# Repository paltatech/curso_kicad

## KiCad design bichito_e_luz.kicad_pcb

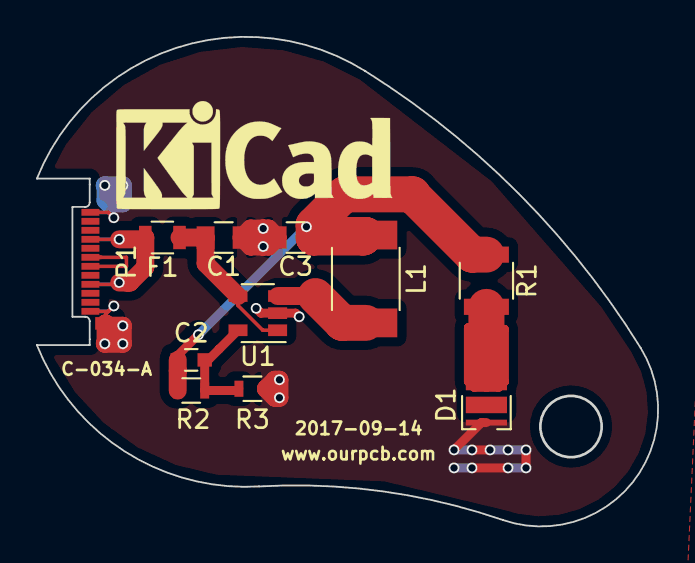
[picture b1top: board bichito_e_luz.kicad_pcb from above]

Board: 2 copper layers, 34.5 x 27.2 mm, 11 parts (0 on the bottom side), 8 nets.

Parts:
C1, C3: 10uF; C_0805
C2: 1nF; C_0603
D1: LED_ALT; LED_Cree-XB
F1: FUSE 1A; R_0805
L1: 10uH; L_1812
P1: USB_C_Plug; USB_C_Plug_Molex_105444
R1: 1R; R_1210
R2: 432k; R_0603
R3: 100k; R_0603
U1: NCP1529; SOT-23-5

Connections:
/supply/VIN: F1.2, P1.A4, P1.A9, P1.B4, P1.B9
/supply/VOUT: C2.1, C3.1, L1.2, R1.1, R2.1
GND: C1.2, C3.2, D1.1, P1.A1, P1.A12, P1.B1, P1.B12, P1.S1, R3.2, U1.2
unnamed: C1.1, F1.1, U1.1, U1.4
unnamed: C2.2, R2.2, R3.1, U1.5
unnamed: D1.2, R1.2
unnamed: L1.1, U1.3
unnamed: P1.A6, P1.A7

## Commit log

2017-09-05 Primer commit. Esquematico a la espera de fuente conmutada
2017-09-08 Esquematico completo. Footprintss asignados
2017-09-14 Termino layout. Despues de la clase agregue silkscreens y un fusible
2017-09-14 Agrego dxf del contorno del pcb
2017-10-03 Add pulldowns updated values and assembly layer
